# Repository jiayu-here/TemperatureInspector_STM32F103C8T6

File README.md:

# STM32F103C8T6 Temperature Inspector

[English](#english) | [中文](#中文)

This is a temperature-monitoring and alarm project for an STM32F103C8T6 minimum-system board. It integrates DS18B20, PT100 voltage acquisition, OLED, keys, a buzzer, alarm LEDs, SD-card logging through FatFs, serial commands, persistent thresholds, and a reserved ESP-01S cloud-service flow.

## Purpose

The project is designed for embedded temperature-monitoring scenarios. It covers sensor acquisition, data display, alarm decisions, data logging, and serial interaction. It can serve as an STM32 course project, a temperature-acquisition system, a sensor-integration experiment, or an embedded-project portfolio piece.

## Highlights

- Supports both the DS18B20 digital temperature sensor and PT100 analog temperature acquisition.
- OLED displays current temperature, thresholds, alarm status, and system information.
- Supports key configuration, buzzer alarms, and alarm-light indications.
- Uses FatFs to write temperature logs to an SD card.
- Provides serial commands for debugging and parameter inspection.
- Threshold parameters persist across power cycles.
- Reserves an ESP-01S cloud-service flow for future network expansion.
- Supports ST-Link programming and a Keil MDK-compatible project structure.

## Project Entry Points

Main project file:

~~~text
Projects/MDK-ARM/TemperatureInspector_STM32F103C8T6.uvprojx
~~~

Detailed documentation:

~~~text
Docs/工程说明书.md
~~~

Generated HEX file:

~~~text
build_gcc/TemperatureInspector.hex
~~~

## Hardware Design

The repository now includes a complete KiCad 10 schematic and four-layer PCB design. The board uses the pin-compatible `STM32F103CBT6` in LQFP-48, measures 100 mm x 80 mm, and implements the firmware pin map for the sensors, display, storage, alarms, ESP-01S, UART, and SWD interfaces.

- Hardware guide and connector pinout: [`Hardware/KiCad/README_Hardware.md`](Hardware/KiCad/README_Hardware.md)
- KiCad project: `Hardware/KiCad/TemperatureInspector_STM32F103C8T6_Hardware.kicad_pro`
- Manufacturing outputs: `Hardware/KiCad/Manufacturing/`
- Verification reports: `Hardware/KiCad/Verification/` (ERC 0 errors/warnings; DRC 0 violations)
- Ready-to-share archives: `TemperatureInspector_STM32F103C8T6_KiCad_Project.zip` and `TemperatureInspector_STM32F103C8T6_Manufacturing.zip`

## Quick Start

1. Complete wiring using the pin table in Docs/工程说明书.md.
2. Format the SD card as FAT32 and insert it into the SD module.
3. Open Projects/MDK-ARM/TemperatureInspector_STM32F103C8T6.uvprojx in Keil.
4. Connect ST-Link to PA13, PA14, GND, and 3.3 V; keep BOOT0 at 0.
5. Build and download, or directly flash build_gcc/TemperatureInspector.hex.

## Default Parameters

~~~text
Temperature sample period: 15 seconds
Threshold-check period: 15 seconds
SD write period: 15 seconds
DS18B20 default alarm range: below 10 C or above 60 C
PT default alarm range: below 0 C or above 100 C
Cloud service: disabled by default; flow retained in code
Alarm confirmation: alarm after 2 consecutive out-of-range readings
~~~

## Directory Guide

| Directory / file | Purpose |
|---|---|
| Inc/ | Application headers and HAL configuration currently in use |
| Src/ | Application source currently in use |
| Core/ | Synchronized backup of application source and headers |
| Projects/MDK-ARM/ | Keil project |
| Middlewares/Third_Party/FatFs/ | FatFs file-system source |
| Drivers/ | STM32 HAL/CMSIS drivers |
| Docs/ | Project manual, CubeMX configuration, and paper analysis |
| Hardware/KiCad/ | KiCad schematic, PCB, previews, manufacturing files, and ERC/DRC reports |
| build_gcc/ | GCC build output, including flashable HEX |
| TemperatureInspector_STM32F103C8T6.ioc | CubeMX configuration file |

## Suitable Uses

- STM32 embedded-systems course project
- Multi-sensor temperature acquisition and alarm system
- Integrated OLED, SD-card, serial, key, and buzzer experiment
- Keil MDK and STM32 HAL project-structure study

## Notes

- PB3/PB4 are used as keys. Keep debugging in Serial Wire mode; do not enable full JTAG.
- Before powering the board, check power, logic levels, sensor wiring, and SD-card formatting.
- The cloud-service flow is reserved and disabled by default; it can be connected to an actual platform later.

# STM32F103C8T6 温度检测仪

[English](#english) | [中文](#中文)

这是一个基于 STM32F103C8T6 最小系统板的温度检测与报警工程。项目已经接入 DS18B20、PT100 电压采集、OLED、按键、蜂鸣器、报警灯、SD 卡 FatFs 记录、串口命令、阈值掉电保存，以及 ESP-01S 云服务预留流程。

## 项目定位

本项目面向嵌入式温度监测场景，重点覆盖传感器采集、数据显示、报警判断、数据记录和串口交互。它既可以作为 STM32 课程设计，也可以作为温度采集系统、传感器综合实验或嵌入式项目作品展示。

## 功能亮点

- 同时支持 DS18B20 数字温度传感器和 PT100 模拟温度采集。
- OLED 显示当前温度、阈值、报警状态和系统信息。
- 支持按键设置、蜂鸣器报警和报警灯提示。
- 使用 FatFs 将温度记录写入 SD 卡。
- 支持串口命令交互，便于调试和参数查看。
- 阈值参数支持掉电保存。
- 预留 ESP-01S 云服务流程，便于后续扩展联网能力。
- 支持 ST-Link 烧录，工程结构适配 Keil MDK。

## 工程入口

主工程文件：

~~~text
Projects/MDK-ARM/TemperatureInspector_STM32F103C8T6.uvprojx
~~~

详细说明文档：

~~~text
Docs/工程说明书.md
~~~

已生成 HEX：

~~~text
build_gcc/TemperatureInspector.hex
~~~

## 硬件设计

仓库现已包含完整的 KiCad 10 原理图和四层 PCB。板上采用与当前固件引脚兼容的 LQFP-48 `STM32F103CBT6`，板框为 100 mm x 80 mm，已经实现传感器、显示、存储、报警、ESP-01S、串口和 SWD 等接口。

- 硬件说明与接口针序：[`Hardware/KiCad/README_Hardware.md`](Hardware/KiCad/README_Hardware.md)
- KiCad 工程：`Hardware/KiCad/TemperatureInspector_STM32F103C8T6_Hardware.kicad_pro`
- 制造文件：`Hardware/KiCad/Manufacturing/`
- 检查报告：`Hardware/KiCad/Verification/`（ERC 0 错误/警告，DRC 0 违规）
- 可直接交付的压缩包：`TemperatureInspector_STM32F103C8T6_KiCad_Project.zip`、`TemperatureInspector_STM32F103C8T6_Manufacturing.zip`

## 快速使用

1. 按 Docs/工程说明书.md 的引脚表完成接线。
2. 将 SD 卡格式化为 FAT32，并插入 SD 模块。
3. 使用 Keil 打开 Projects/MDK-ARM/TemperatureInspector_STM32F103C8T6.uvprojx。
4. 用 ST-Link 连接 PA13、PA14、GND、3.3V，BOOT0 保持 0。
5. 编译并下载，或直接烧录已生成的 build_gcc/TemperatureInspector.hex。

## 当前默认参数

~~~text
测温周期：15 秒
阈值判断周期：15 秒
SD 写入周期：15 秒
DS18B20 默认报警阈值：低于 10 C 或高于 60 C
PT 默认报警阈值：低于 0 C 或高于 100 C
云服务：默认关闭，代码流程保留
报警确认：连续 2 次超阈值才报警
~~~

## 目录说明

| 目录/文件 | 作用 |
|---|---|
| Inc/ | 当前实际使用的应用头文件和 HAL 配置 |
| Src/ | 当前实际使用的应用源码 |
| Core/ | 同步备份的应用源码/头文件 |
| Projects/MDK-ARM/ | Keil 工程 |
| Middlewares/Third_Party/FatFs/ | FatFs 文件系统源码 |
| Drivers/ | STM32 HAL/CMSIS 驱动 |
| Docs/ | 工程说明、CubeMX 配置、论文分析 |
| Hardware/KiCad/ | KiCad 原理图、PCB、预览图、制造文件和 ERC/DRC 报告 |
| build_gcc/ | GCC 编译输出，含可烧录 HEX |
| TemperatureInspector_STM32F103C8T6.ioc | CubeMX 配置文件 |

## 适用场景

- STM32 嵌入式课程设计。
- 多传感器温度采集与报警系统。
- OLED、SD 卡、串口、按键和蜂鸣器综合实验。
- Keil MDK + STM32 HAL 工程结构学习。

## 注意事项

- PB3/PB4 用作按键，所以调试方式必须保持 Serial Wire，不要启用完整 JTAG。
- 上板前建议先检查供电、电平、传感器接线和 SD 卡格式。
- 云服务流程目前为预留状态，默认关闭，后续可继续接入实际平台。

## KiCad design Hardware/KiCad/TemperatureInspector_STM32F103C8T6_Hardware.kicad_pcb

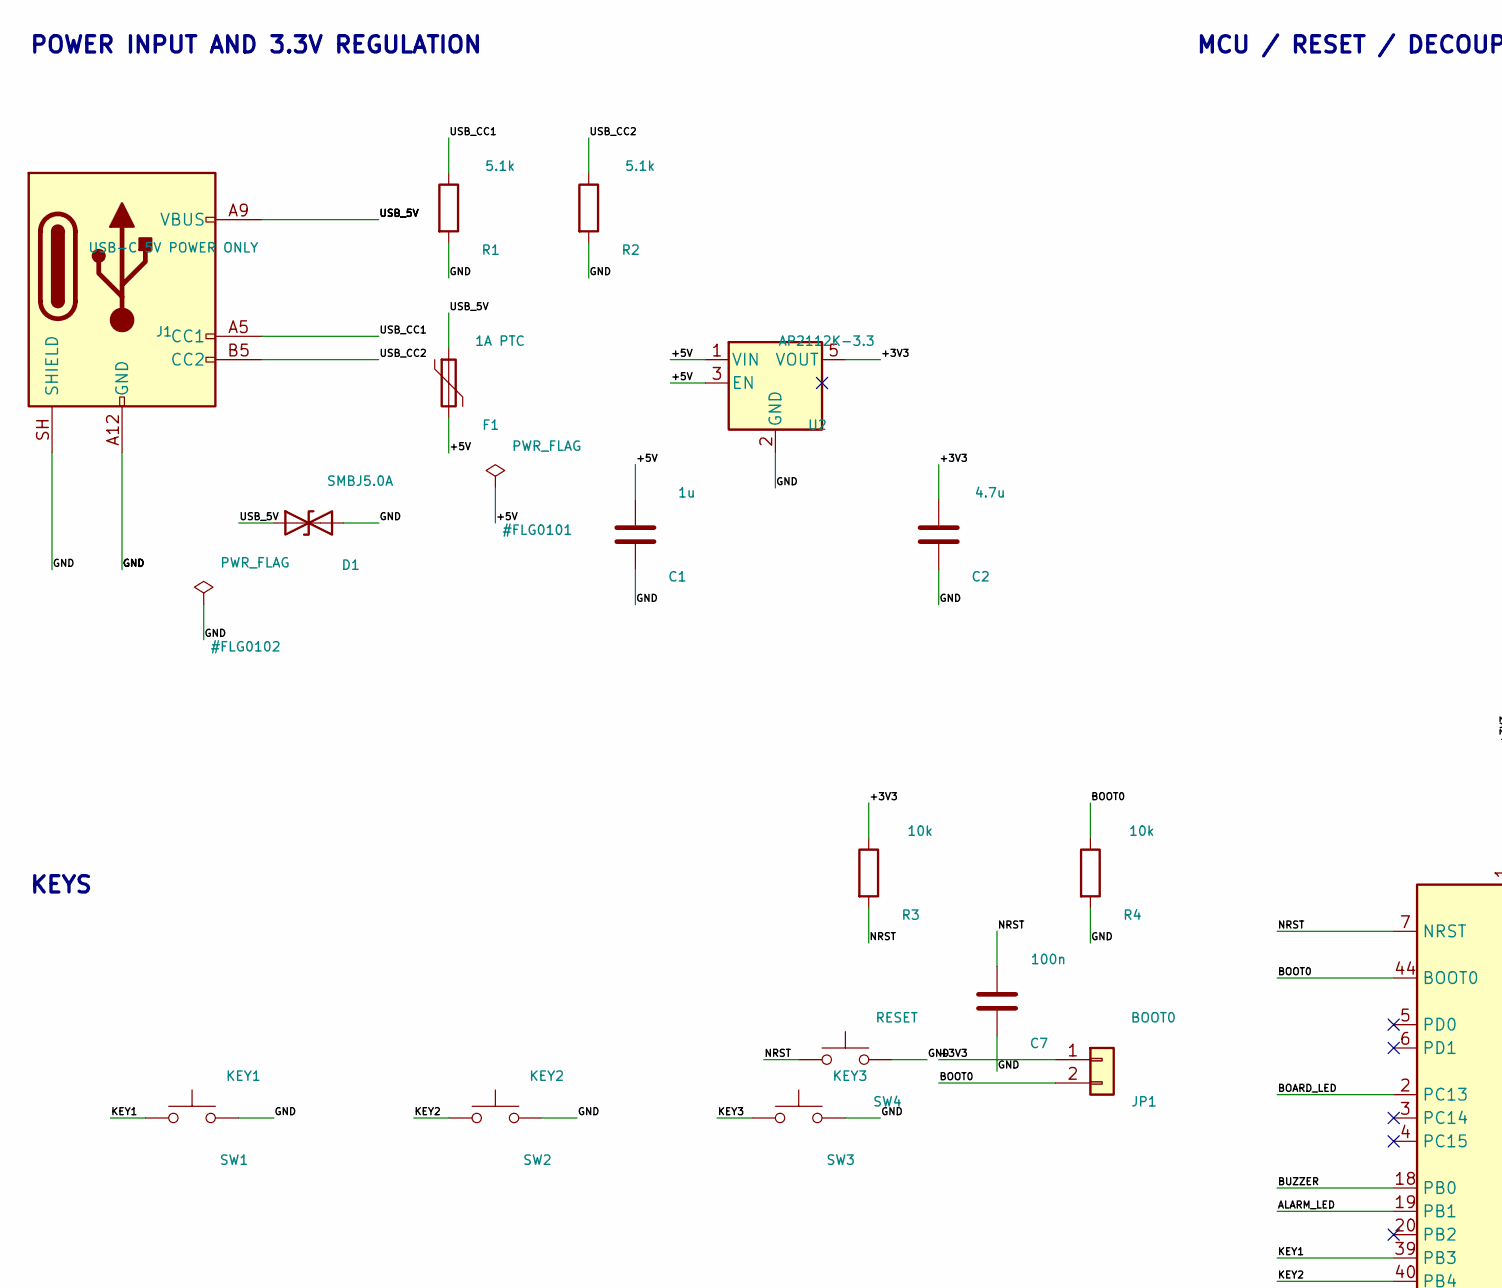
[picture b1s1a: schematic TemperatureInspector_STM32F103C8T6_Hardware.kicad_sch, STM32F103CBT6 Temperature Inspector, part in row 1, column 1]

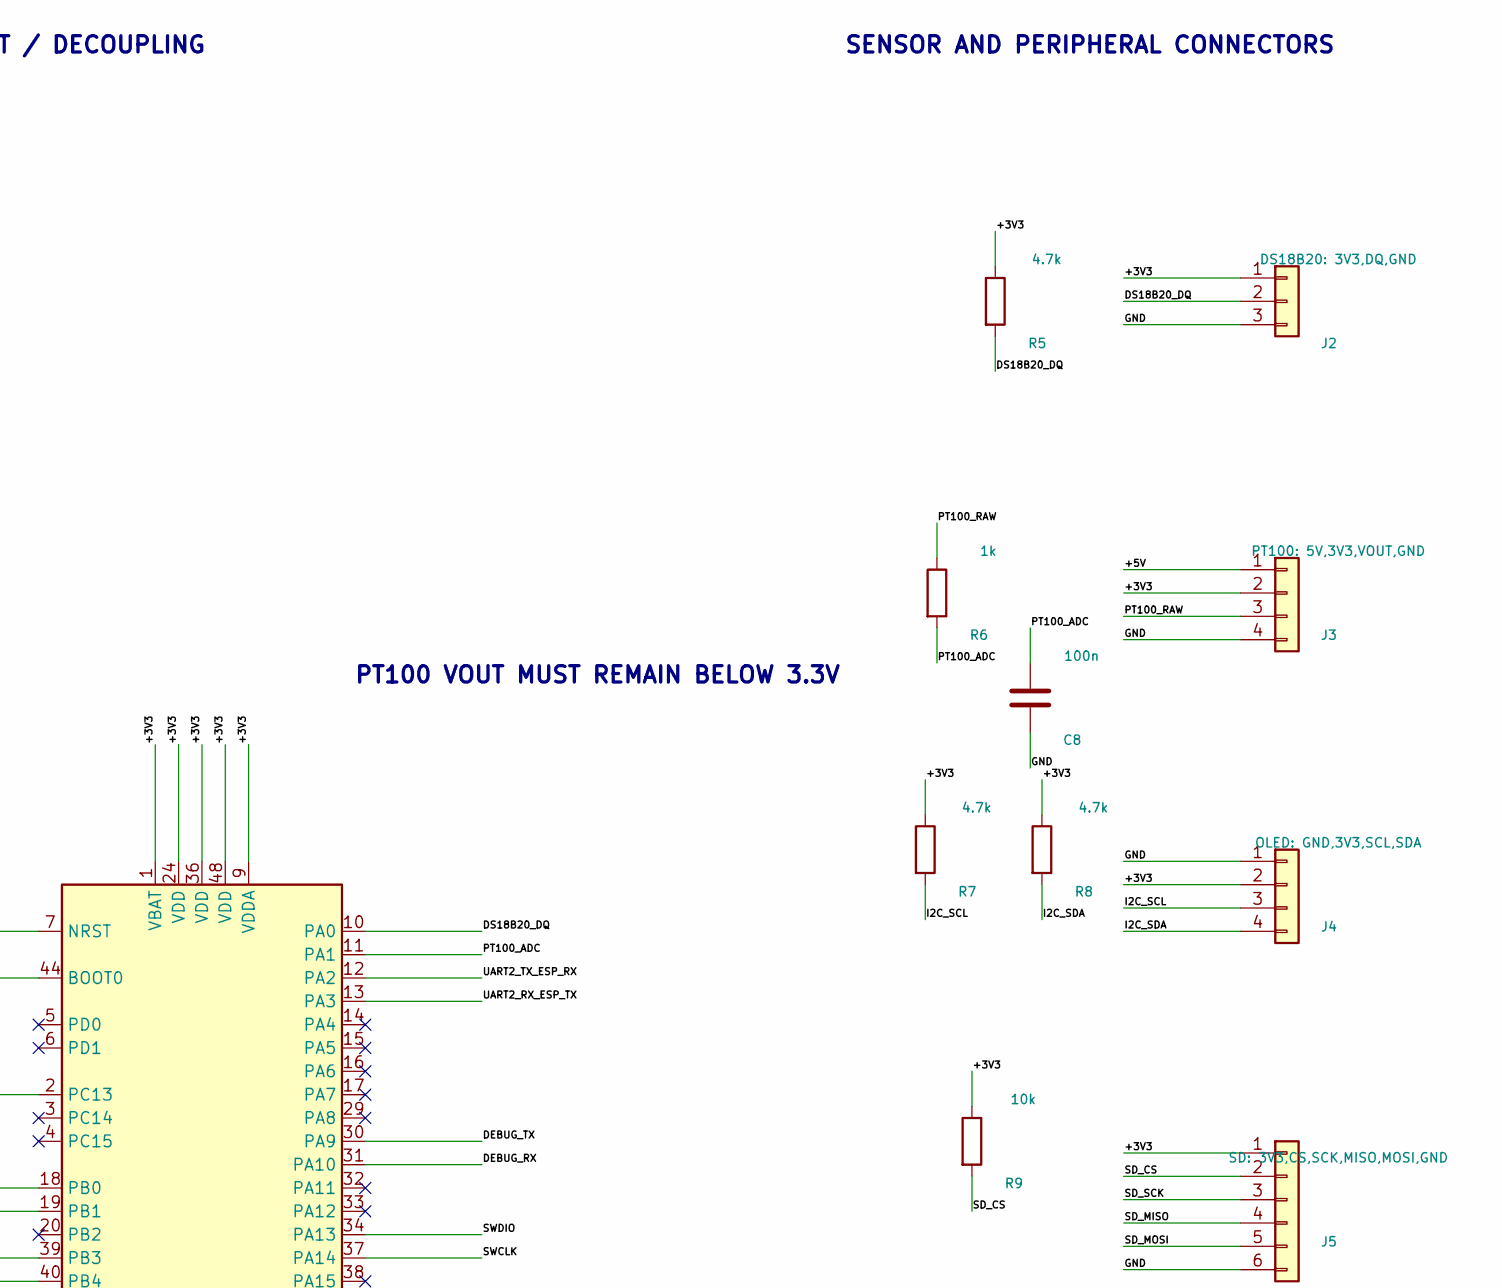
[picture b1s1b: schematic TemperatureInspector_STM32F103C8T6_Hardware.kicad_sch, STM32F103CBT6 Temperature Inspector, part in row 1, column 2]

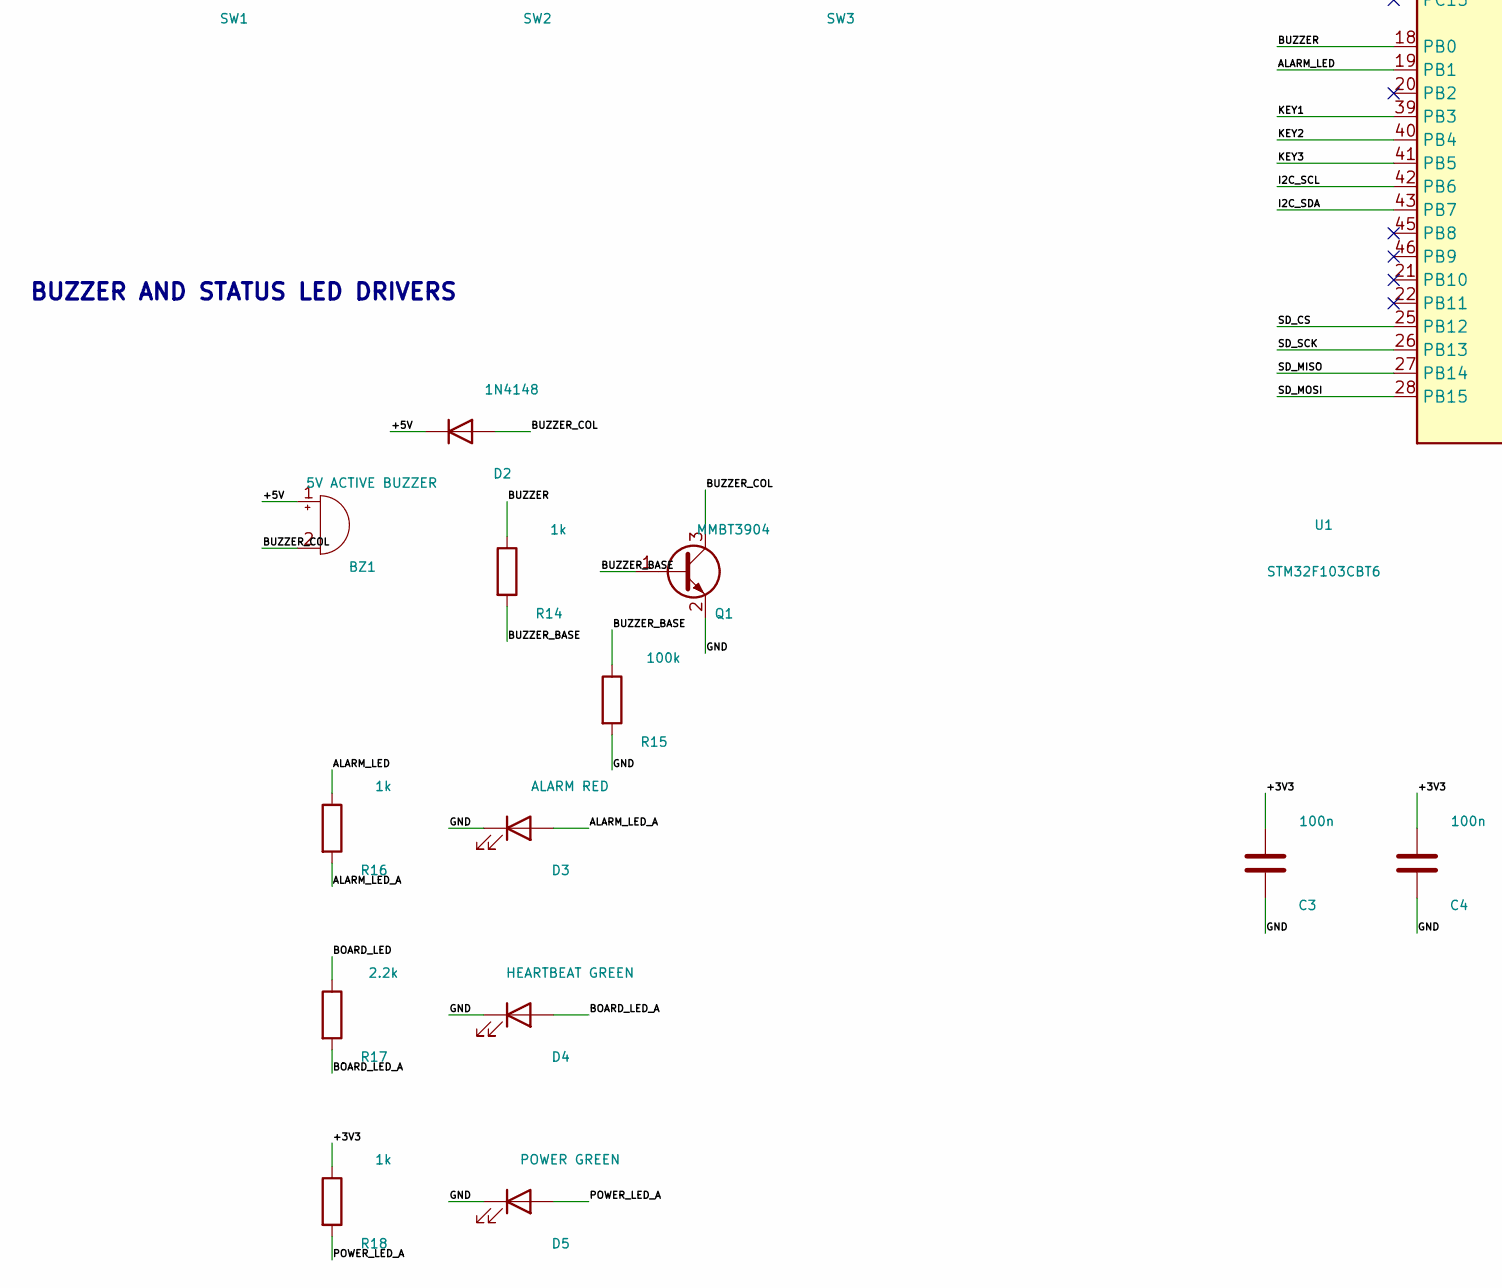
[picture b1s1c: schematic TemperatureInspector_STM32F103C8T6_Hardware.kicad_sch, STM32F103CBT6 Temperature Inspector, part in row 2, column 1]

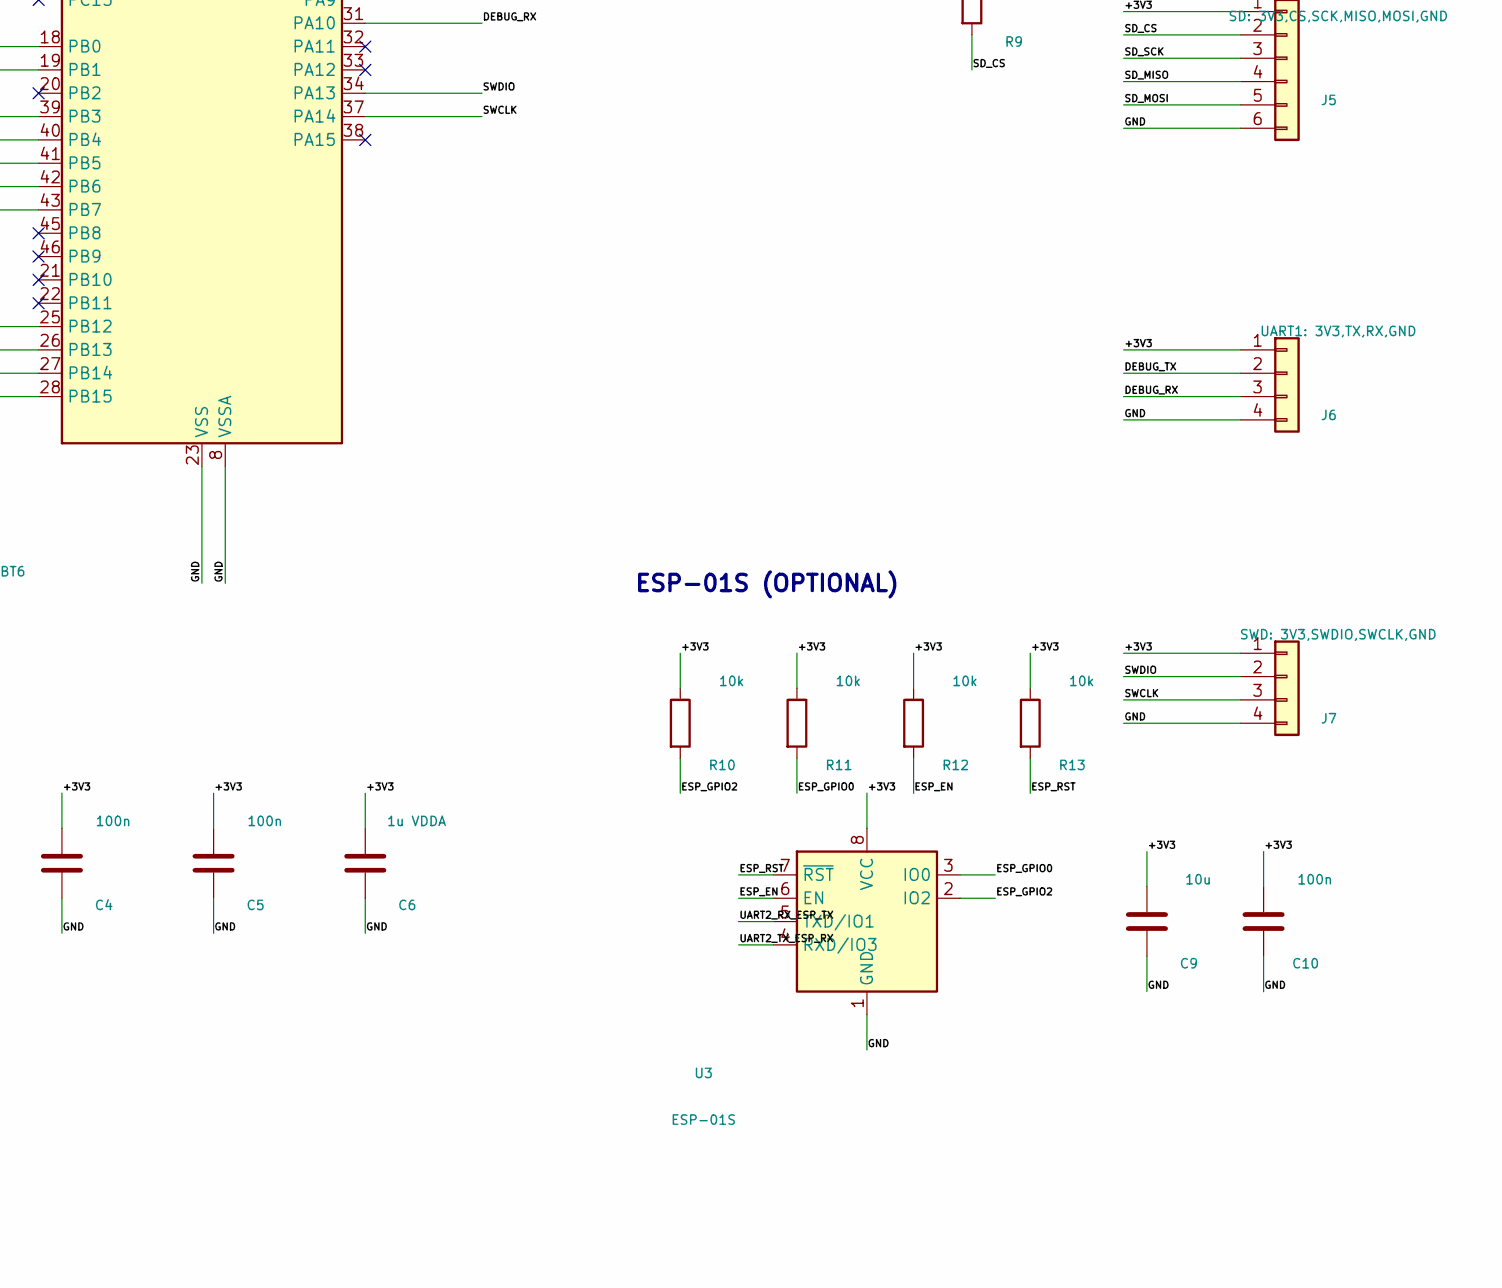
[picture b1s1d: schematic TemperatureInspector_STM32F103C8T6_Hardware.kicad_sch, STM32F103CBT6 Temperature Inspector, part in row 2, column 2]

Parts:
BZ1: 5V ACTIVE BUZZER; Buzzer_12x9.5RM7.6
C1: 1u; C_0603_1608Metric
C2: 4.7u; C_0805_2012Metric
C3, C4, C5, C7, C8, C10: 100n; C_0603_1608Metric
C6: 1u VDDA; C_0603_1608Metric
C9: 10u; C_0805_2012Metric
D1: SMBJ5.0A; D_SMA
D2: 1N4148; D_SOD-123
D3: ALARM RED; LED_0603_1608Metric
D4: HEARTBEAT GREEN; LED_0603_1608Metric
D5: POWER GREEN; LED_0603_1608Metric
F1: 1A PTC; Fuse_1206_3216Metric
J1: USB-C 5V POWER ONLY; USB_C_Receptacle_GCT_USB4125-xx-x_6P_TopMnt_Horizontal
J2: DS18B20: 3V3,DQ,GND; PinHeader_1x03_P2.54mm_Vertical
J3: PT100: 5V,3V3,VOUT,GND; PinHeader_1x04_P2.54mm_Vertical
J4: OLED: GND,3V3,SCL,SDA; PinHeader_1x04_P2.54mm_Vertical
J5: SD: 3V3,CS,SCK,MISO,MOSI,GND; PinHeader_1x06_P2.54mm_Vertical
J6: UART1: 3V3,TX,RX,GND; PinHeader_1x04_P2.54mm_Vertical
J7: SWD: 3V3,SWDIO,SWCLK,GND; PinHeader_1x04_P2.54mm_Vertical
JP1: BOOT0; PinHeader_1x02_P2.54mm_Vertical
Q1: MMBT3904; SOT-23
R1, R2: 5.1k; R_0603_1608Metric
R3, R4, R9, R10, R11, R12, R13: 10k; R_0603_1608Metric
R5, R7, R8: 4.7k; R_0603_1608Metric
R6, R14, R16, R18: 1k; R_0603_1608Metric
R15: 100k; R_0603_1608Metric
R17: 2.2k; R_0603_1608Metric
SW1: KEY1; SW_PUSH_6mm
SW2: KEY2; SW_PUSH_6mm
SW3: KEY3; SW_PUSH_6mm
SW4: RESET; SW_PUSH_6mm
U1: STM32F103CBT6; LQFP-48_7x7mm_P0.5mm
U2: AP2112K-3.3; SOT-23-5
U3: ESP-01S; ESP-01

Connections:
/+3V3: C2.1, C3.1, C4.1, C5.1, C6.1, C9.1, C10.1, J2.1, J3.2, J4.2, J5.1, J6.1, J7.1, JP1.1, R3.1, R5.1, R7.1, R8.1, R9.1, R10.1, R11.1, R12.1, R13.1, R18.1, U1.1 (VBAT), U1.9 (VDDA), U1.24 (VDD), U1.36 (VDD), U1.48 (VDD), U2.5 (VOUT), U3.8 (VCC)
/+5V: BZ1.1 (+), C1.1, D2.1 (K), F1.2, J3.1, U2.1 (VIN), U2.3 (EN)
/ALARM_LED: R16.1, U1.19 (PB1)
/ALARM_LED_A: D3.2 (A), R16.2
/BOARD_LED: R17.1, U1.2 (PC13)
/BOARD_LED_A: D4.2 (A), R17.2
/BOOT0: JP1.2, R4.1, U1.44 (BOOT0)
/BUZZER: R14.1, U1.18 (PB0)
/BUZZER_BASE: Q1.1 (B), R14.2, R15.1
/BUZZER_COL: BZ1.2 (-), D2.2 (A), Q1.3 (C)
/DEBUG_RX: J6.3, U1.31 (PA10)
/DEBUG_TX: J6.2, U1.30 (PA9)
/DS18B20_DQ: J2.2, R5.2, U1.10 (PA0)
/ESP_EN: R12.2, U3.6 (EN)
/ESP_GPIO0: R11.2, U3.3 (IO0)
/ESP_GPIO2: R10.2, U3.2 (IO2)
/ESP_RST: R13.2, U3.7 (~RST)
/GND: C1.2, C2.2, C3.2, C4.2, C5.2, C6.2, C7.2, C8.2, C9.2, C10.2, D1.2 (A2), D3.1 (K), D4.1 (K), D5.1 (K), J1.A12 (GND), J1.B12 (GND), J1.SH (SHIELD), J2.3, J3.4, J4.1, J5.6, J6.4, J7.4, Q1.2 (E), R1.2, R2.2, R4.2, R15.2, SW1.2, SW2.2, SW3.2, SW4.2, U1.8 (VSSA), U1.23 (VSS), U1.35 (VSS), U1.47 (VSS), U2.2 (GND), U3.1 (GND)
/I2C_SCL: J4.3, R7.2, U1.42 (PB6)
/I2C_SDA: J4.4, R8.2, U1.43 (PB7)
/KEY1: SW1.1, U1.39 (PB3)
/KEY2: SW2.1, U1.40 (PB4)
/KEY3: SW3.1, U1.41 (PB5)
/NRST: C7.1, R3.2, SW4.1, U1.7 (NRST)
/POWER_LED_A: D5.2 (A), R18.2
/PT100_ADC: C8.1, R6.2, U1.11 (PA1)
/PT100_RAW: J3.3, R6.1
/SD_CS: J5.2, R9.2, U1.25 (PB12)
/SD_MISO: J5.4, U1.27 (PB14)
/SD_MOSI: J5.5, U1.28 (PB15)
/SD_SCK: J5.3, U1.26 (PB13)
/SWCLK: J7.3, U1.37 (PA14)
/SWDIO: J7.2, U1.34 (PA13)
/UART2_RX_ESP_TX: U1.13 (PA3), U3.5 (TXD/IO1)
/UART2_TX_ESP_RX: U1.12 (PA2), U3.4 (RXD/IO3)
/USB_5V: D1.1 (A1), F1.1, J1.A9 (VBUS), J1.B9 (VBUS)
/USB_CC1: J1.A5 (CC1), R1.1
/USB_CC2: J1.B5 (CC2), R2.1

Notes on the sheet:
POWER INPUT AND 3.3V REGULATION
BUZZER AND STATUS LED DRIVERS
KEYS
PT100 VOUT MUST REMAIN BELOW 3.3V
SENSOR AND PERIPHERAL CONNECTORS
MCU / RESET / DECOUPLING
ESP-01S (OPTIONAL)

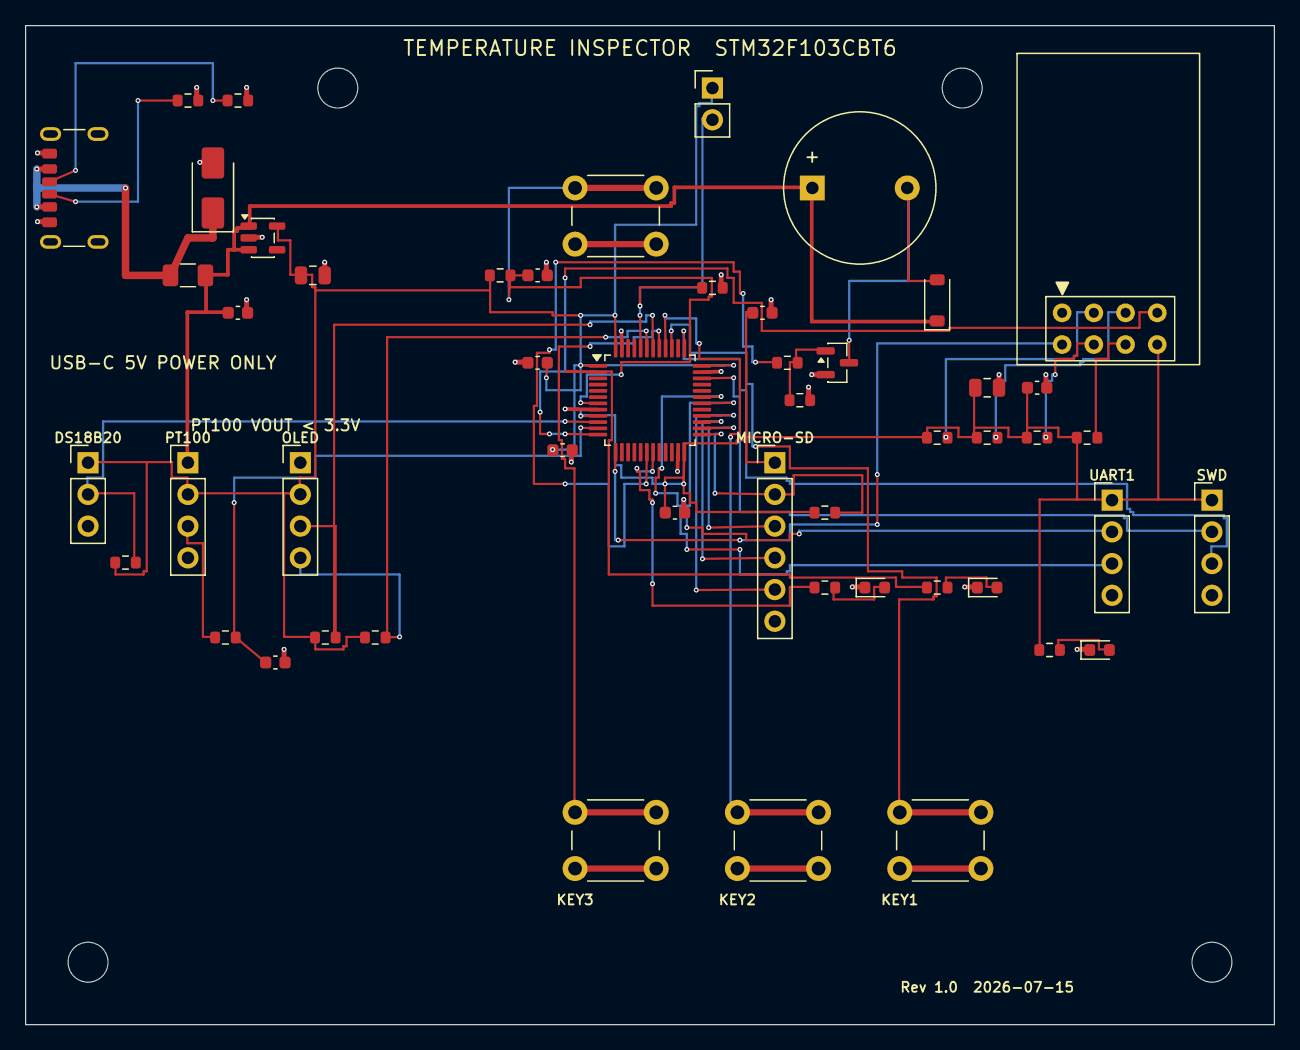
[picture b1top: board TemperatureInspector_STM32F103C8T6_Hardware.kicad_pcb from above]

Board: 4 copper layers, 100.0 x 80.0 mm, 55 parts (0 on the bottom side), 38 nets.

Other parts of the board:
H1, H2, H3, H4: M3; MountingHole_3.2mm_M3

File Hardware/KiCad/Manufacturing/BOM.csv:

"Reference","Value","Footprint","Quantity"
"BZ1","5V ACTIVE BUZZER","Buzzer_Beeper:Buzzer_12x9.5RM7.6","1"
"C1","1u","Capacitor_SMD:C_0603_1608Metric","1"
"C2","4.7u","Capacitor_SMD:C_0805_2012Metric","1"
"C3-C5,C7,C8,C10","100n","Capacitor_SMD:C_0603_1608Metric","6"
"C6","1u VDDA","Capacitor_SMD:C_0603_1608Metric","1"
"C9","10u","Capacitor_SMD:C_0805_2012Metric","1"
"D1","SMBJ5.0A","Diode_SMD:D_SMA","1"
"D2","1N4148","Diode_SMD:D_SOD-123","1"
"D3","ALARM RED","LED_SMD:LED_0603_1608Metric","1"
"D4","HEARTBEAT GREEN","LED_SMD:LED_0603_1608Metric","1"
"D5","POWER GREEN","LED_SMD:LED_0603_1608Metric","1"
"F1","1A PTC","Fuse:Fuse_1206_3216Metric","1"
"J1","USB-C 5V POWER ONLY","Connector_USB:USB_C_Receptacle_GCT_USB4125-xx-x_6P_TopMnt_Horizontal","1"
"J2","DS18B20: 3V3,DQ,GND","Connector_PinHeader_2.54mm:PinHeader_1x03_P2.54mm_Vertical","1"
"J3","PT100: 5V,3V3,VOUT,GND","Connector_PinHeader_2.54mm:PinHeader_1x04_P2.54mm_Vertical","1"
"J4","OLED: GND,3V3,SCL,SDA","Connector_PinHeader_2.54mm:PinHeader_1x04_P2.54mm_Vertical","1"
"J5","SD: 3V3,CS,SCK,MISO,MOSI,GND","Connector_PinHeader_2.54mm:PinHeader_1x06_P2.54mm_Vertical","1"
"J6","UART1: 3V3,TX,RX,GND","Connector_PinHeader_2.54mm:PinHeader_1x04_P2.54mm_Vertical","1"
"J7","SWD: 3V3,SWDIO,SWCLK,GND","Connector_PinHeader_2.54mm:PinHeader_1x04_P2.54mm_Vertical","1"
"JP1","BOOT0","Connector_PinHeader_2.54mm:PinHeader_1x02_P2.54mm_Vertical","1"
"Q1","MMBT3904","Package_TO_SOT_SMD:SOT-23","1"
"R1,R2","5.1k","Resistor_SMD:R_0603_1608Metric","2"
"R3,R4,R9-R13","10k","Resistor_SMD:R_0603_1608Metric","7"
"R5,R7,R8","4.7k","Resistor_SMD:R_0603_1608Metric","3"
"R6,R14,R16,R18","1k","Resistor_SMD:R_0603_1608Metric","4"
"R15","100k","Resistor_SMD:R_0603_1608Metric","1"
"R17","2.2k","Resistor_SMD:R_0603_1608Metric","1"
"SW1","KEY1","Button_Switch_THT:SW_PUSH_6mm","1"
"SW2","KEY2","Button_Switch_THT:SW_PUSH_6mm","1"
"SW3","KEY3","Button_Switch_THT:SW_PUSH_6mm","1"
"SW4","RESET","Button_Switch_THT:SW_PUSH_6mm","1"
"U1","STM32F103CBT6","Package_QFP:LQFP-48_7x7mm_P0.5mm","1"
"U2","AP2112K-3.3","Package_TO_SOT_SMD:SOT-23-5","1"
"U3","ESP-01S","RF_Module:ESP-01","1"

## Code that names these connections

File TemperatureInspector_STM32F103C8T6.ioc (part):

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Mcu.Name=STM32F103C(8-B)Tx
Mcu.Package=LQFP48
Mcu.UserName=STM32F103CBTx
PA0-WKUP.GPIOParameters=GPIO_Label
PA0-WKUP.GPIO_Label=DS18B20_DQ
PA0-WKUP.Signal=GPIO_Output
PA1.Signal=ADCx_IN1
PA10.Signal=USART1_RX
PA13.Signal=SYS_JTMS-SWDIO
PA14.Signal=SYS_JTCK-SWCLK
PA2.Signal=USART2_TX
PA3.Signal=USART2_RX
PA9.Signal=USART1_TX
PB0.GPIOParameters=GPIO_Label
PB0.GPIO_Label=BUZZER
PB0.Signal=GPIO_Output
PB1.GPIOParameters=GPIO_Label
PB1.GPIO_Label=ALARM_LED
PB1.Signal=GPIO_Output
PB12.GPIOParameters=GPIO_Label
PB12.GPIO_Label=SD_CS
PB12.Signal=GPIO_Output
PB13.Signal=SPI2_SCK
PB14.Signal=SPI2_MISO
PB15.Signal=SPI2_MOSI
PB3.GPIOParameters=GPIO_PuPd,GPIO_Label
PB3.GPIO_Label=KEY1
PB3.GPIO_PuPd=GPIO_PULLUP
PB3.Signal=GPIO_Input
PB4.GPIOParameters=GPIO_PuPd,GPIO_Label
PB4.GPIO_Label=KEY2
PB4.GPIO_PuPd=GPIO_PULLUP
PB4.Signal=GPIO_Input
PB5.GPIOParameters=GPIO_PuPd,GPIO_Label
PB5.GPIO_Label=KEY3
PB5.GPIO_PuPd=GPIO_PULLUP
PB5.Signal=GPIO_Input
PB6.Signal=I2C1_SCL
PB7.Signal=I2C1_SDA
PC13-TAMPER-RTC.GPIOParameters=GPIO_Label
PC13-TAMPER-RTC.GPIO_Label=BOARD_LED
PC13-TAMPER-RTC.Signal=GPIO_Output
board=custom

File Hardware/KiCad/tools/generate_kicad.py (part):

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
# ESP-01S module and required boot pull-ups.
add(part("U3", "RF_Module:ESP-01", "ESP-01S", "RF_Module:ESP-01", (10900, 9300), (88, 28), 0,
         {1: "GND", 2: "ESP_GPIO2", 3: "ESP_GPIO0", 4: "UART2_TX_ESP_RX",
          5: "UART2_RX_ESP_TX", 6: "ESP_EN", 7: "ESP_RST", 8: "+3V3"}))
for ref, net, schx, pc in [
    ("R10", "ESP_GPIO2", 10100, (78, 38)), ("R11", "ESP_GPIO0", 10600, (82, 38)),
    ("R12", "ESP_EN", 11100, (86, 38)), ("R13", "ESP_RST", 11600, (90, 38)),
]:
    add(part(ref, "Device:R", "10k", "Resistor_SMD:R_0603_1608Metric", (schx, 8450), pc, 0,
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    order = [
        "PT100_ADC", "PT100_RAW",
        "UART2_TX_ESP_RX", "UART2_RX_ESP_TX", "DEBUG_TX", "DEBUG_RX",
        "ESP_GPIO2", "ESP_GPIO0", "ESP_EN", "ESP_RST",
        "BUZZER", "BUZZER_BASE", "BUZZER_COL", "ALARM_LED", "ALARM_LED_A", "POWER_LED_A",
    ]
    for name in order:
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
